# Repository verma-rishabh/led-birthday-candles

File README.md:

# led-birthday-candles
Light up 7 segment birthday candles with led lighter and blow them....
This project uses msp430g2553 micocontroller to control leds arranged in 7 segment fashion.
The led lighter is used to write number in 7 segment fashion.
Led's initially work as photodiode.
Once lit leds's flicker as candles.
led's can be blown off as a real candles by sensing the temperature change using thermister.

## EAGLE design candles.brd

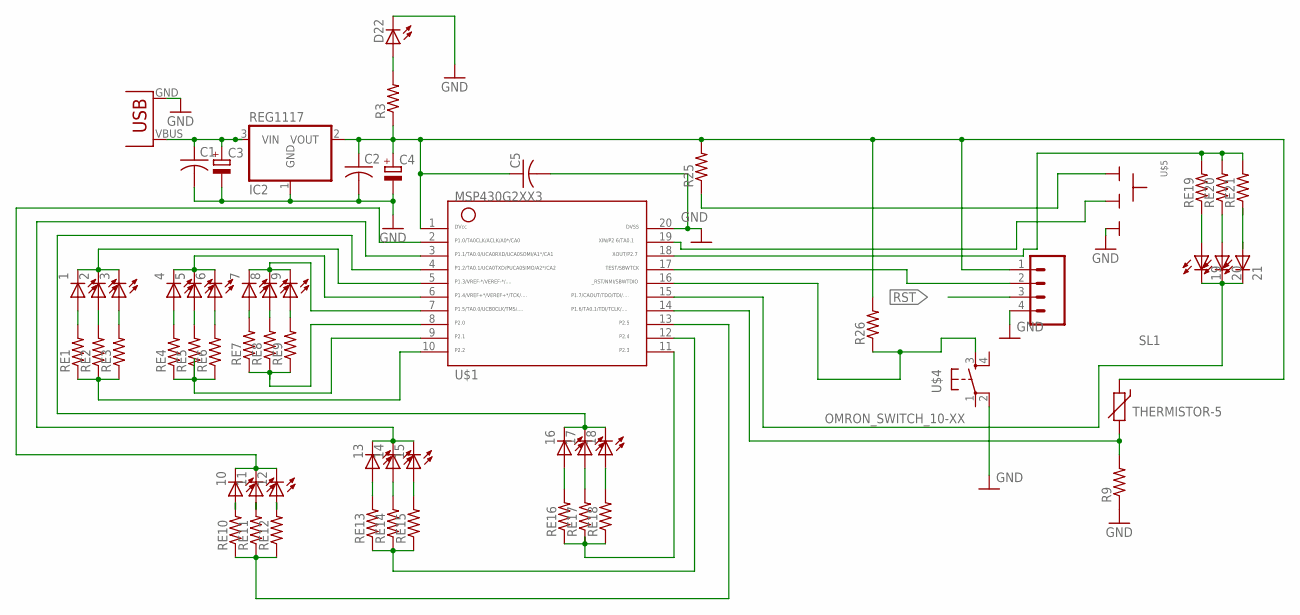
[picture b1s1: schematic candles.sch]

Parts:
1, 2, 3, 4, 5, 6, 7, 8, 9, 10, 11, 12, 13, 14, 15, 16, 17, 18, 19, 20, 21: LED3MM
C1, C2, C5: C-US025-025X050; C025-025X050
C3, C4: CPOL-EUE2.5-7; E2,5-7
D22: LED3MM
IC2: REG1117; SOT223
R3, R9, R25, R26: R-US_0204/7; 0204/7
R8: THERMISTOR-5; R-5
RE1, RE2, RE3, RE4, RE5, RE6, RE7, RE8, RE9, RE10, RE11, RE12, RE13, RE14, RE15, RE16, RE17, RE18, RE19, RE20, RE21: R-US_0204/7; 0204/7
SL1: M04; 04P
U$1: MSP430G2553DIP20; G2553-DIP20
U$2: USB(POWER)
U$4: OMRON_SWITCH_10-XX; B3F-10XX
U$5: SLIDESWITCH-BIG; BIGSWITCH

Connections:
GND: C1.2, C2.2, C3.-, C4.-, C5.2, D22.K (C), IC2.1 (GND), R9.1, SL1.4, U$1.20, U$2.GND, U$4.2 (P1), U$5.3
unnamed: 7.K (C), 8.K (C), 9.K (C), U$1.7
unnamed: 3.A, RE3.2
unnamed: 10.K (C), 11.K (C), 12.K (C), U$1.2
unnamed: 2.A, RE2.2
unnamed: RE7.1, RE8.1, RE9.1, U$1.8
unnamed: 4.A, RE4.2
unnamed: 1.K (C), 2.K (C), 3.K (C), U$1.5
unnamed: RE1.1, RE2.1, RE3.1, U$1.10
unnamed: 4.K (C), 5.K (C), 6.K (C), U$1.6
unnamed: 5.A, RE5.2
unnamed: 13.K (C), 14.K (C), 15.K (C), U$1.3
unnamed: 21.A, RE21.1
unnamed: 16.K (C), 17.K (C), 18.K (C), U$1.4
unnamed: SL1.2, U$1.17
unnamed: 20.A, RE20.1
unnamed: RE13.1, RE14.1, RE15.1, U$1.12
unnamed: R25.1, U$5.1
unnamed: 19.K (C), 20.K (C), 21.K (C), U$1.15
unnamed: RE19.2, RE20.2, RE21.2, U$1.18
unnamed: R8.2, R9.2, U$1.14
unnamed: 1.A, RE1.2
unnamed: C1.1, C3.+, IC2.3 (VIN), U$2.VBUS (VCC)
unnamed: D22.A, R3.2
unnamed: 6.A, RE6.2
unnamed: RE4.1, RE5.1, RE6.1, U$1.9
unnamed: 7.A, RE7.2
unnamed: 8.A, RE8.2
unnamed: 9.A, RE9.2
unnamed: RE10.1, RE11.1, RE12.1, U$1.13
unnamed: U$1.19, U$5.2
unnamed: RE16.1, RE17.1, RE18.1, U$1.11
unnamed: 10.A, RE10.2
unnamed: 11.A, RE11.2
unnamed: 12.A, RE12.2
unnamed: 13.A, RE13.2
unnamed: 14.A, RE14.2
unnamed: 15.A, RE15.2
unnamed: 16.A, RE16.2
unnamed: 17.A, RE17.2
unnamed: 18.A, RE18.2
unnamed: C2.1, C4.+, C5.1, IC2.2 (VOUT), R3.1, R8.1, R25.2, R26.2, SL1.1, U$1.1
unnamed: 19.A, RE19.1
RST: R26.1, SL1.3, U$1.16, U$4.3 (S)

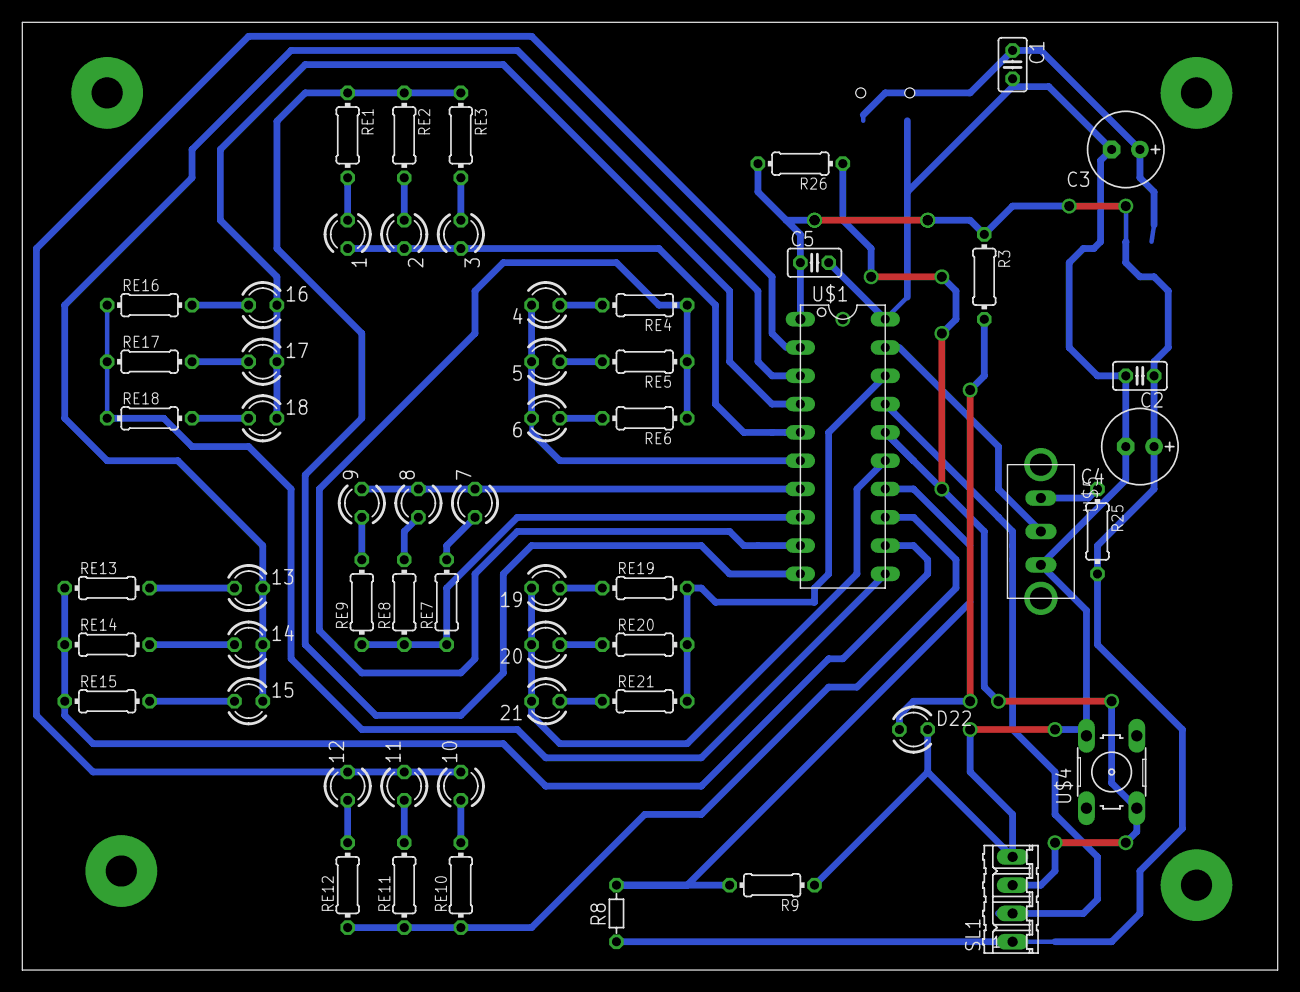
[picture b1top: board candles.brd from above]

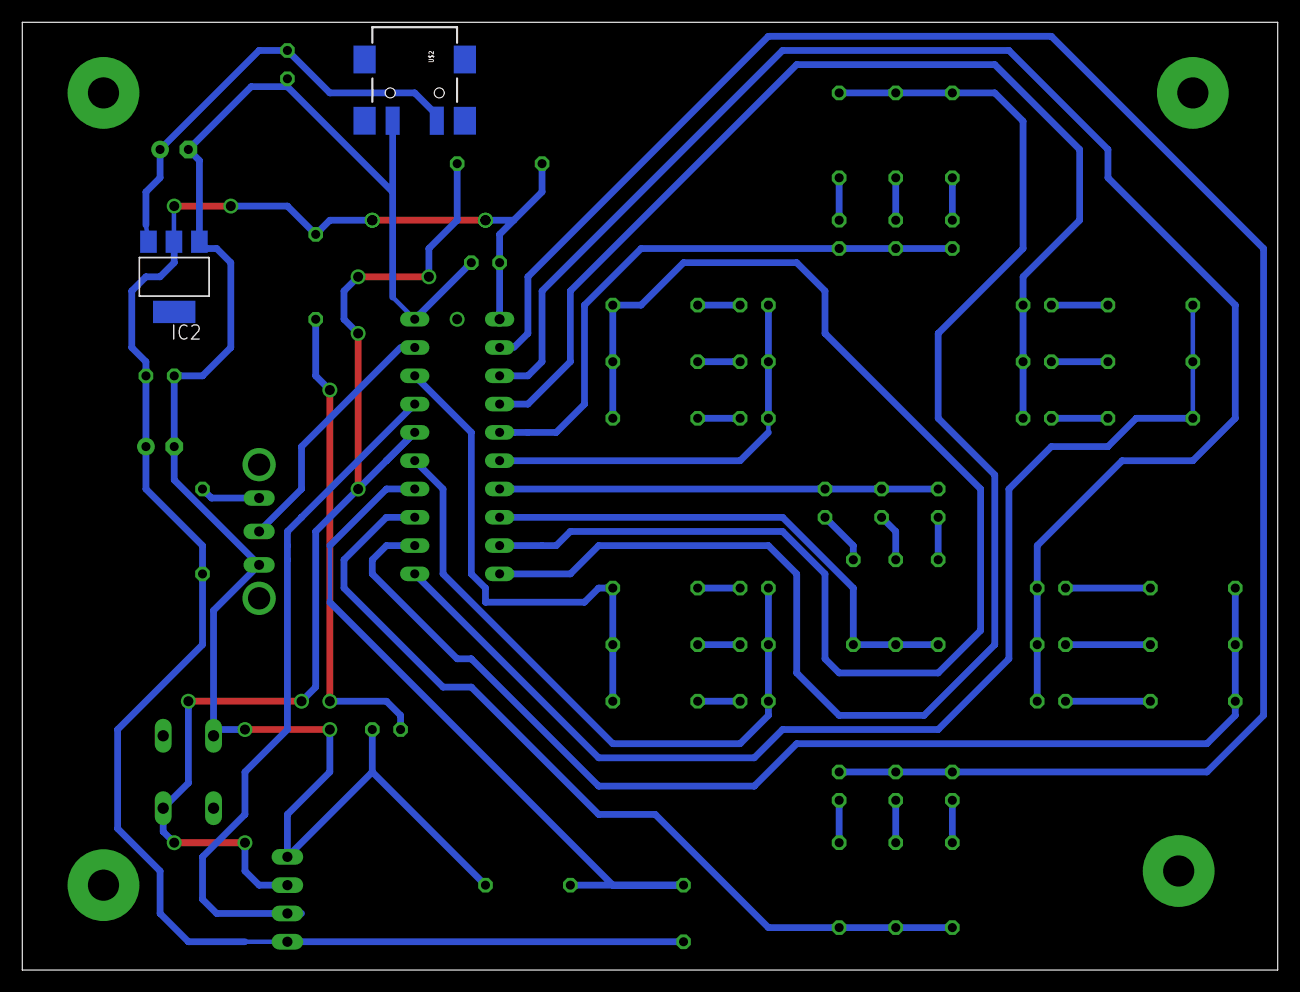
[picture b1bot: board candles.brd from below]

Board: 2 copper layers, 112.7 x 85.1 mm, 59 parts (2 on the bottom side), 44 nets.

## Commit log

2016-12-30 Rename birth1.brd2.brd3.brd to candles.brd
2016-12-30 Rename birth1.brd2.sch to candles.sch
